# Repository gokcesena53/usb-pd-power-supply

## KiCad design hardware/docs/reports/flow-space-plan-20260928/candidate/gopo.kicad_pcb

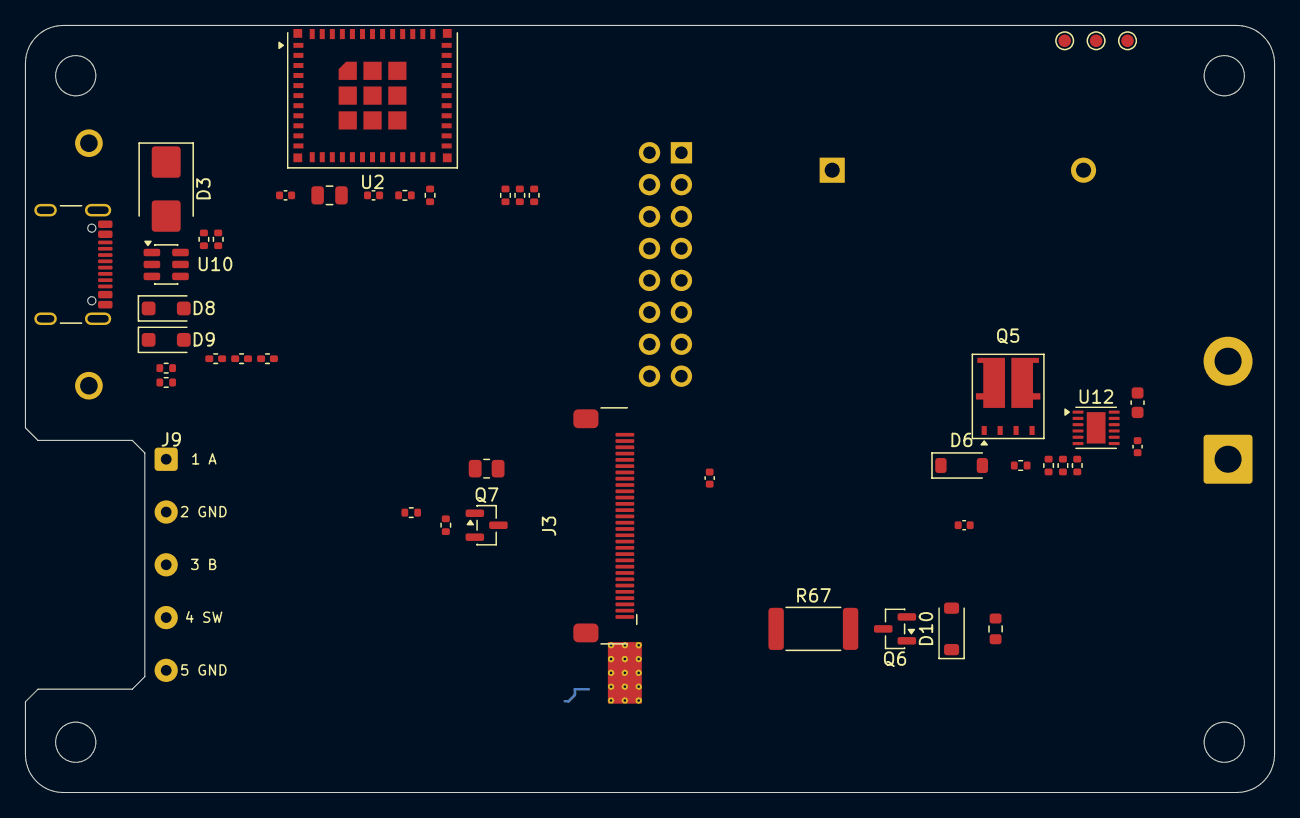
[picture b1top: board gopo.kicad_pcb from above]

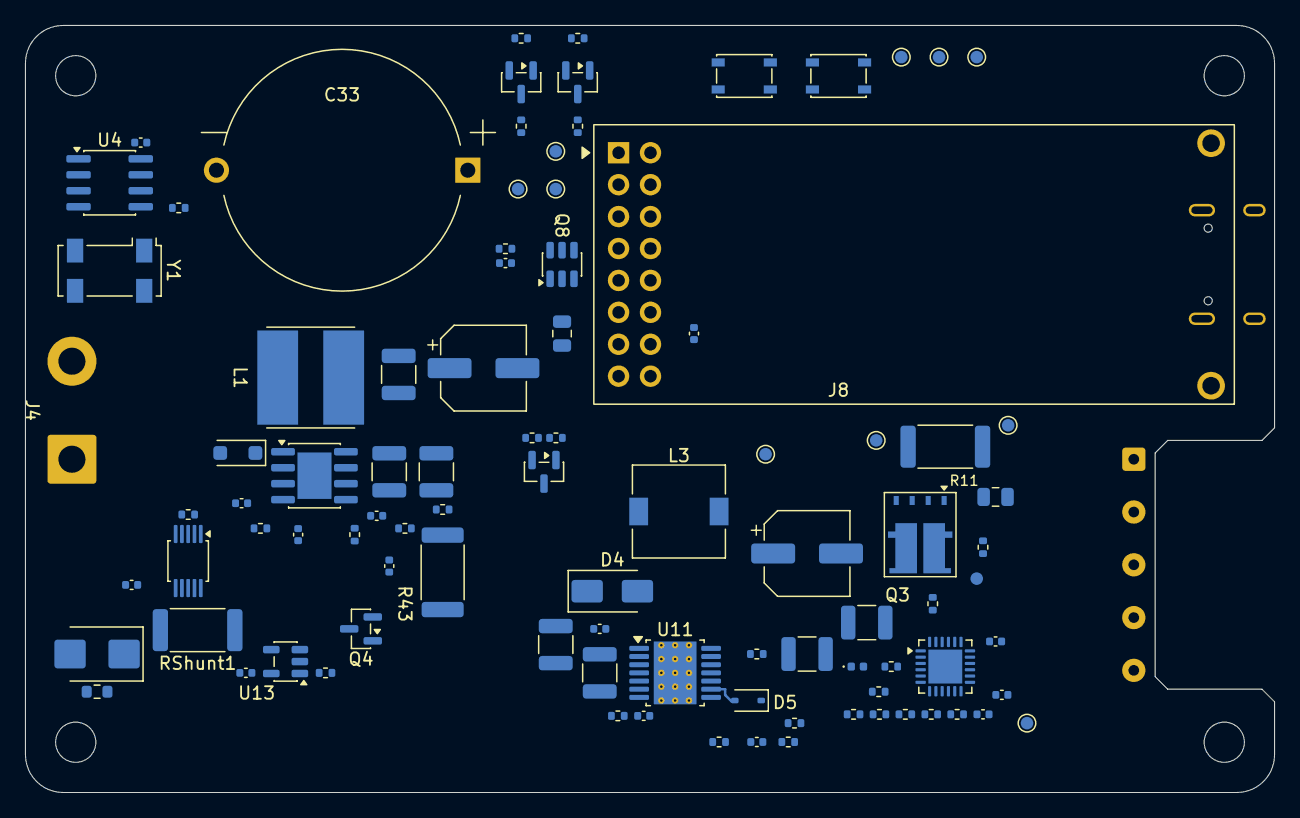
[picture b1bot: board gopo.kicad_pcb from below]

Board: 4 copper layers, 99.4 x 61.0 mm, 144 parts (94 on the bottom side), 86 nets.

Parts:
C1, C2, C6, C11, C14, C17, C20, C21, C24, C26, C32, C35: 100n; C_0402_1005Metric
C3: 2u2; C_0805_2012Metric
C4, C7, C9, C34: 1u0; C_0402_1005Metric
C5, C10: 22u; C_0805_2012Metric
C8, C12, C13, C25, C27, C28: 4u7; C_1210_3225Metric
C15, C29: 47u; CP_Elec_6.3x5.8
C16: 47u; C_1210_3225Metric
C18: 10n; C_0402_1005Metric
C19: 15n; C_0402_1005Metric
C23: 47n; C_0402_1005Metric
C30: 22n; C_0402_1005Metric
C31: 220n; C_0603_1608Metric
C33: 1F5; Korchip_DCL_H-Type_D19.0mm_P20.00mm_Horizontal
D1: LED; LED_0402_1005Metric
D2: SS2060FL; D_SOD-123F
D3, D7: SMBJ30A; D_SMB
D4: SX36; D_SMA
D5: BAS16H; D_SOD-323
D6, D10: BZT52C12; D_SOD-123
D8, D9: SMF30A; D_SOD-123F
H1, H2, H3, H4: M3; MountingHole_3.2mm_M3
J3: TFT032B018; KLS_L-KLS1-242I-2.0-30_1x30-2MP_P0.50mm_Horizontal
J4: SolderWire-1.5sqmm; SolderWire-1.5sqmm_1x02_P7.8mm_D1.7mm_OD3.9mm
J7: USB_C_Receptacle_USB2.0_16P; USB_C_Receptacle_GCT_USB4105-xx-A_16P_TopMnt_Horizontal
J8: 2-CH UART TO ETH; Waveshare_2-CH_UART_TO_ETH
J9: ENCODER CABLE; SolderWire-0.25sqmm_1x05_P4.2mm_D0.65mm_OD1.7mm
L1: 22u; L_CoreMaster_FPI0705_7.8x7.0mm_H5.0
L3: 6u8; L_7.3x7.3_H4.5
MECH_ENC: PANEL EC1121S; J9 cable
Q1, Q2, Q4, Q6: BSS138P; SOT-23
Q3, Q5: SQJB60EP; Vishay_PowerPAK_SO-8L_Dual
Q7: IRLML6344; SOT-23
Q8: TSM3443CX6; SOT-23-6
R1, R8, R9, R10, R16, R27, R34, R35, R36, R37, R56, R65: 10k; R_0402_1005Metric
R2, R3, R15: 22R; R_0402_1005Metric
R4, R5, R6, R7, R24, R61: 4k7; R_0402_1005Metric
R11: 5m0; R_2512_6332Metric
R12: 6k2; R_0402_1005Metric
R13, R28: 100R; R_0402_1005Metric
R14: 2k2; R_0402_1005Metric
R17, R21, R29, R38, R53, R58: 100k; R_0402_1005Metric
R39: 10k2; R_0402_1005Metric
R40: 3k24; R_0402_1005Metric
R41: 51k; R_0402_1005Metric
R43: 4k7; R_2512_6332Metric
R47: 78k7; R_0402_1005Metric
R48: 30k1; R_0402_1005Metric
R49, R51: 9k76; R_0402_1005Metric
R50: 2k87; R_0402_1005Metric
R52, R64: 2k0; R_0402_1005Metric
R54: 1k0; R_0402_1005Metric
R55: 237k; R_0402_1005Metric
R59, R66: 100k; R_0603_1608Metric
R60: 5R6; R_0805_2012Metric
R62, R63: 5k1; R_0402_1005Metric
R67: 1k; R_2512_6332Metric
RShunt1: 5m0; R_2512_6332Metric
SW1: BOOT / PTS810; SW_SPST_PTS810
SW2: RESET / PTS810; SW_SPST_PTS810
TH1: 10k NTC; R_0402_1005Metric
TP1, TP2, TP3, TP4, TP5, TP6, TP7, TP8, TP9, TP10, TP11, TP12, TP13, TP14: TestPoint; TestPoint_Pad_D1.0mm
U1: AP33772SDKZ-13-FA02; Texas_RTW_WQFN-24-1EP_4x4mm_P0.5mm_EP2.7x2.7mm
U2: ESP32-C6-MINI-1-H4; ESP32-C6-MINI-1
U3: INA226; TSSOP-10_3x3mm_P0.5mm
U4: BQ32000; SOIC-8_3.9x4.9mm_P1.27mm
U5: AOZ1284PI; SOIC-8-1EP_3.9x4.9mm_P1.27mm_EP2.71x3.7mm
U6: TLV431BQDBZT; SOT-23
U10: USBLC6-2SC6; SOT-23-6
U11: TPS55340PWPR; Texas_HTSSOP-14-1EP_4.4x5mm_P0.65mm_EP3.4x5mm_Mask3.155x3.2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
U12: LM74801-Q1; WSON-12-1EP_3x3mm_P0.5mm_EP1.5x2.5mm
U13: 74LVC1G08; SOT-23-5
Y1: 32.768kHz; Crystal_SMD_Abracon_ABS25-4Pin_8.0x3.8mm

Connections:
+3.3V: C5.1, C6.1, C9.1, C11.1, C15.1, C16.1, C21.1, C34.1, C35.1, J3.21, J3.22, J3.23, L1.2, Q1.1 (G), Q2.1 (G), Q8.4, R1.1, R4.2, R7.1, R10.2, R17.1, R24.1, R27.1, R34.1, R35.1, R36.1, R37.2, R39.1, R60.1, U2.3, U3.6 (VS), U4.8, U10.5, U13.5
/MCU/ETH_3V3: C10.1, C20.1, J8.13, J8.14, Q8.1, Q8.2, Q8.5, Q8.6
/MCU/ETH_CFG0: J8.3, R15.2, TP9.1 (1_1)
/MCU/ETH_PWR_EN: C21.2, Q8.3, R16.1, R17.2, TP10.1 (1_1)
/MCU/ETH_RUN: J8.4, TP14.1
/MCU/RTC_INT: R24.2, U2.5, U4.7
/MCU/UART_RX: J8.7, TP12.1, U2.30
/MCU/UART_TX: J8.5, TP11.1, U2.31
/USB_PD_CONTROLLER/BOOST_FB: D5.2, R48.2, R49.1, U11.9
/USB_PD_CONTROLLER/BOOST_SW: D4.2, L3.1, U11.1, U11.2
/USB_PD_CONTROLLER/COMP_NODE: R41.1, U5.5 (COMP)
/USB_PD_CONTROLLER/DGATE: Q5.4, U12.1
/USB_PD_CONTROLLER/DISCH_G: D10.1, Q4.3, Q6.1, R66.2
/USB_PD_CONTROLLER/EN_CTRL: D5.1, R43.2, R50.1, U5.8 (EN), U6.2 (REF)
/USB_PD_CONTROLLER/FB_3V3: R39.2, R40.1, U5.6 (FB)
/USB_PD_CONTROLLER/FSW_SET: R38.1, U5.4 (FSW)
/USB_PD_CONTROLLER/GATE_DRV: D6.1, Q5.2, R54.1, U12.8
/USB_PD_CONTROLLER/LX_SW: C17.2, D2.1 (K), L1.1, U5.1 (LX)
/USB_PD_CONTROLLER/OV_SENSE: R55.2, R56.1, U12.5
/USB_PD_CONTROLLER/PD_GATE: Q3.2, Q3.4, R12.2, TP5.1 (1_1)
/USB_PD_CONTROLLER/PD_VBUS_SENSED: C3.1, Q3.7, Q3.8, Q5.7, Q5.8, R11.2, R55.1, TP2.1 (1_1), U1.24 (VCC)
/USB_PD_CONTROLLER/SRC_COMMON: D6.2, Q5.1, Q5.3, U12.2, U12.9
/USB_PD_CONTROLLER/SS_RAMP: C18.1, U5.7 (SS)
/USB_PD_CONTROLLER/SW_EN: Q4.1, R58.1, U12.6, U13.4
/USB_PD_CONTROLLER/SW_OUT: Q5.5, Q5.6, R66.1, RShunt1.1, U3.10 (Vin+), U12.12
/USER INTERFACE/BL_A: J3.2, R60.2
/USER INTERFACE/BL_K: J3.4, Q7.3
ENCODER_A: J9.1, R34.2, U2.28
ENCODER_B: J9.3, R35.2, U2.29
ENCODER_SW: J9.4, R36.2, U2.27
GND: C1.2, C2.2, C3.2, C4.2, C5.2, C6.2, C7.1, C8.2, C9.2, C10.2, C11.2, C12.2, C13.2, C14.2, C15.2, C16.2, C18.2, C19.2, C20.2, C23.2, C24.2, C25.2, C26.2, C27.2, C28.2, C29.2, C30.2, C32.2, C33.2, C34.2, C35.2, D1.1 (K), D2.2 (A), D3.2, D7.2, D8.2, D9.2, D10.2, J3.5, J3.7, J3.8, J3.9, J3.10, J3.11, J3.12, J3.13, J3.14, J3.15, J3.25, J3.30, J4.2, J7.A1 (GND), J7.A12 (GND), J7.B1 (GND), J7.B12 (GND), J7.SH (SHIELD), J8.11, J8.12, J9.2, J9.5, Q4.2, Q6.2, Q7.2, R21.1, R29.2, R38.2, R40.2, R47.2, R49.2, R51.2, R56.2, R58.2, R59.2, R61.2, R62.2, R63.2, R65.2, SW1.1, SW2.1, TH1.1, TP13.1, U1.3 (GND), U1.25 (GND), U2.1, U2.2, U2.11, U2.14, U2.36, U2.37, U2.38, U2.39, U2.40, U2.41, U2.42, U2.43, U2.44, U2.45, U2.46, U2.47, U2.48, U2.49, U2.50, U2.51, U2.52, U2.53, U3.1 (A1), U3.2 (A0), U3.7 (GND), U4.4, U5.3 (GND), U6.3 (A), U10.2, U11.6, U11.7, U11.11, U11.12, U11.13, U11.14, U11.15, U12.7, U13.3, Y1.2, Y1.3
INA_ALERT: R27.2, U2.6, U3.3 (~Alert), U13.2
unnamed: C19.1, R41.2
unnamed: C24.1, R52.2
unnamed: C30.1, R54.2
unnamed: D1.2 (A), R14.2
unnamed: Q3.1, Q3.3
unnamed: Q6.3, R67.2
unnamed: Q7.1, R28.2, R29.1
unnamed: R8.2, R64.1
unnamed: R9.2, R65.1
unnamed: C2.1, U1.15 (IFB)
unnamed: R14.1, U1.8 (LED)
unnamed: TH1.2, U1.13 (OTP)
unnamed: R12.1, U1.23 (PWR_EN)
unnamed: C1.1, U1.12 (V18)
unnamed: R13.1, U1.22 (VOUT)
unnamed: R21.2, U1.11 (VSEL)
unnamed: C7.2, R1.2, SW2.2, U2.8
unnamed: R16.2, U2.12
unnamed: R15.1, R37.1, U2.22
unnamed: R10.1, SW1.2, U2.23
unnamed: R2.1, U2.17
unnamed: R3.1, U2.18
unnamed: U4.1, Y1.1
unnamed: U4.2, Y1.4
unnamed: C33.1, U4.3
unnamed: C17.1, U5.2 (BST)
unnamed: R50.2, R51.1, U6.1 (K)
unnamed: R52.1, U11.8
unnamed: R53.2, U11.4
unnamed: R47.1, U11.10
unnamed: C23.1, U11.5
unnamed: C31.2, U12.11
OUT_EN: R61.1, U2.15, U13.1
OUT_POS: D7.1, J4.1, R59.1, R67.1, RShunt1.2, U3.8 (Vbus), U3.9 (Vin-)
PD_5V: C4.1, R5.1, R6.1, TP4.1 (1_1), U1.20 (V5V)
PD_I2C_SCL_3V3: Q1.2 (S), R4.1, TP6.1 (1_1), U2.24, U3.5 (SCL), U4.6
PD_I2C_SCL_5V: Q1.3 (D), R5.2, U1.5 (SCL)
PD_I2C_SDA_3V3: Q2.2 (S), R7.2, TP7.1 (1_1), U2.25, U3.4 (SDA), U4.5
PD_I2C_SDA_5V: Q2.3 (D), R6.2, U1.4 (SDA)
PD_INT_3V3: R9.1, R64.2, TP8.1 (1_1), U2.26
PD_INT_5V: R8.1, U1.9 (INT)
PD_VOUT: C8.1, C25.1, C26.1, C29.1, L3.2, Q3.5, Q3.6, R13.2, R53.1, TP3.1 (1_1), U11.3
TFT_BL_PWM: R28.1, U2.13
TFT_CS: J3.18, U2.19
TFT_DC: J3.16, U2.16
TFT_MOSI: J3.19, U2.10
TFT_RST: J3.20, U2.20
TFT_SCLK: J3.17, U2.9
USB_CC1: D8.1, J7.A5 (CC1), R62.1, U1.17 (CC1)
USB_CC2: D9.1, J7.B5 (CC2), R63.1, U1.16 (CC2)
USB_DM: J7.A7 (D-), J7.B7 (D-), R2.2, U10.1, U10.6
USB_DP: J7.A6 (D+), J7.B6 (D+), R3.2, U10.3, U10.4
USB_VBUS: D3.1, J7.A4 (VBUS), J7.A9 (VBUS), J7.B4 (VBUS), J7.B9 (VBUS), R11.1, TP1.1 (1_1), U1.1 (ISENP)
V_PRE: C12.1, C13.1, C14.1, C27.1, C28.1, C31.1, C32.1, D4.1, R43.1, R48.1, U5.9 (VIN), U12.3, U12.4, U12.10

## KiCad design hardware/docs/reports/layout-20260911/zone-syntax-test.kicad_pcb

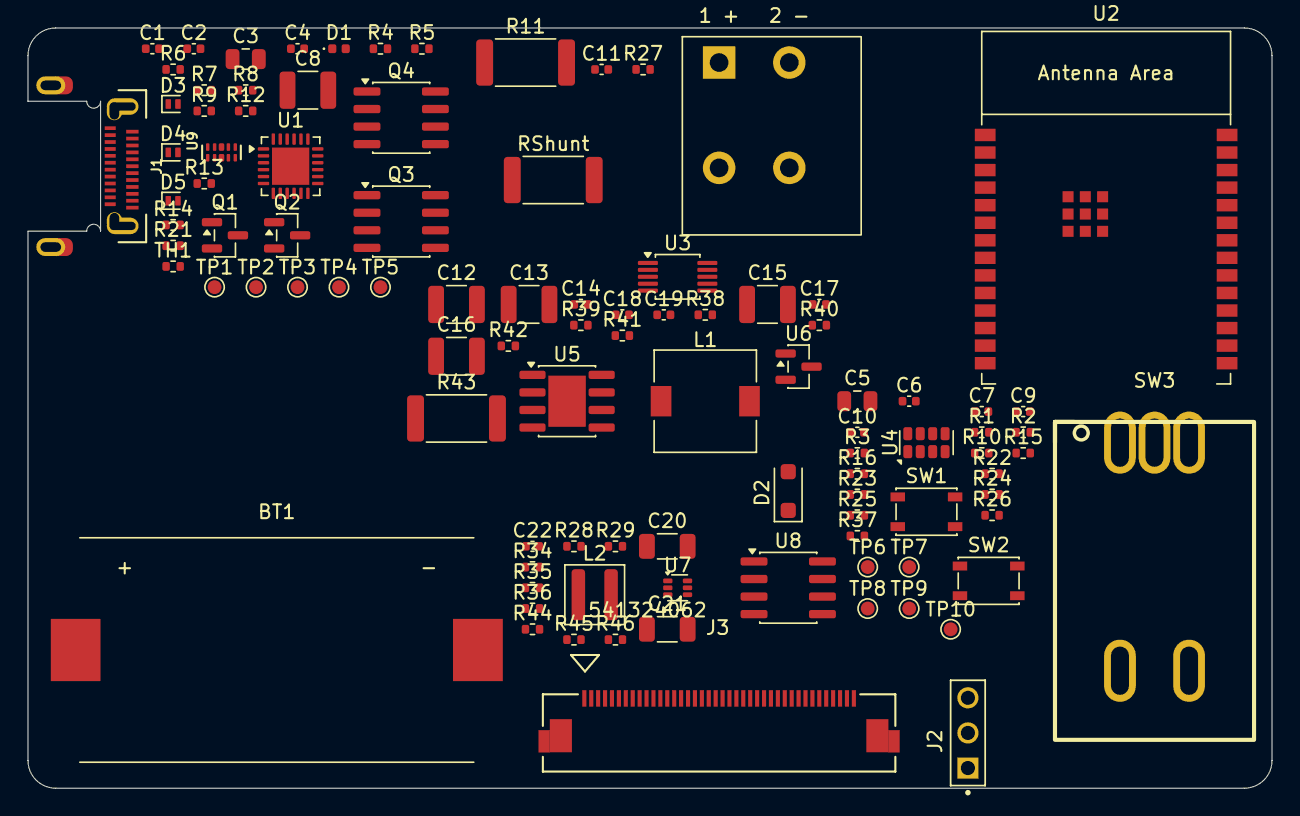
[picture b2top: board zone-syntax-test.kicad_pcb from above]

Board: 4 copper layers, 90.0 x 55.0 mm, 100 parts (0 on the bottom side), 70 nets, no tracks yet.

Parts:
BT1: CR2032 holder; KLS_CR2032_05
C1, C2: 100 nF; C_0402_1005Metric
C3: 1uF / 50V; C_0805_2012Metric
C4: 1uF / 10V; C_0402_1005Metric
C5: 22uF; C_0805_2012Metric
C6, C9, C10, C11, C14: 100nF; C_0402_1005Metric
C7: 1uF; C_0402_1005Metric
C8: 10uF / 50V; C_1210_3225Metric
C12, C13: 10uF; C_1210_3225Metric
C15, C16: 47uF; C_1210_3225Metric
C17, C22: 100nF / 16V; C_0402_1005Metric
C18: 10nF; C_0402_1005Metric
C19: 18nF / 16V; C_0402_1005Metric
C20, C21: 22uF; C_1206_3216Metric
D1: LED; LED_0402_1005Metric
D2: SS2060FL_R1_00001; D_SOD-123F
D3, D4, D5: AQ3130E-01ETG (bidirectional); D_SOD-882
J1: DX07B024JJ1R1500; JAE_DX07B024JJ1R1500
J2: DS1021-1X3SF11-B; CONNFLY_DS1021-1X3SF11-B
J3: NHD-2.4-240320AF-CSXP; CON_541324062_MOL
J4: DG142R-5.08-02P-14-00AH
L1: SRI0704-220M; L_7.3x7.3_H4.5
L2: 2.2uH; L_Wuerth_MAPI-4030
Q1, Q2: BSS138; SOT-23
Q3, Q4: IRF7855TRPBF; SOIC-8_3.9x4.9mm_P1.27mm
R1: 10 kΩ; R_0402_1005Metric
R2, R3: 22Ω; R_0402_1005Metric
R4: 4.7 kΩ; R_0402_1005Metric
R5: 4.7kΩ; R_0402_1005Metric
R6: 4.7 k; R_0402_1005Metric
R7, R25: 4.7k; R_0402_1005Metric
R8: 12k; R_0402_1005Metric
R9: 20k; R_0402_1005Metric
R10, R23, R34, R35, R36: 10k; R_0402_1005Metric
R11: 5mR / 1W; R_2512_6332Metric
R12: 6.2k; R_0402_1005Metric
R13, R28: 100R; R_0402_1005Metric
R14: 2.2k; R_0402_1005Metric
R15: 22 R; R_0402_1005Metric
R16: 22R; R_0402_1005Metric
R21: 100K; R_0402_1005Metric
R22: 1K; R_0402_1005Metric
R24: 4,7k; R_0402_1005Metric
R26: 4.7K; R_0402_1005Metric
R27: 10K; R_0402_1005Metric
R29, R42: 100kR; R_0402_1005Metric
R37: 10kR; R_0402_1005Metric
R38: 100kR 1%; R_0402_1005Metric
R39: 10kR 0.1%; R_0402_1005Metric
R40: 3.20kR 0.1%; R_0402_1005Metric
R41: 12.7kR 1%; R_0402_1005Metric
R43: 1kR / 2W; R_2512_6332Metric
R44: 604kR 0.1%; R_0402_1005Metric
R45: 100kR 0.1%; R_0402_1005Metric
R46: 3.24kR 0.1%; R_0402_1005Metric
RShunt: 5mR / 1W; R_2512_6332Metric
SW1: BOOT / PTS810; SW_SPST_PTS810
SW2: RESET / PTS810; SW_SPST_PTS810
SW3: L-KLS4-EC12-012424-W
TH1: TSM0B103F3381RZ / 10k NTC; R_0402_1005Metric
TP1, TP2, TP3, TP4, TP5, TP6, TP7, TP8, TP9, TP10: TestPoint; TestPoint_Pad_D1.0mm
U1: AP33772SDKZ-13-FA02; Texas_RTW_WQFN-24-1EP_4x4mm_P0.5mm_EP2.7x2.7mm
U2: ESP32-C6-WROOM-1
U3: INA228; TSSOP-10_3x3mm_P0.5mm
U4: RV-3028-C7; MicroCrystal_C7_SON-8_1.5x3.2mm_P0.9mm
U5: AOZ1284PI; SOIC-8-1EP_3.9x4.9mm_P1.27mm_EP2.71x3.7mm
U6: TL431BIDBZR; SOT-23
U7: TPS61023DRLR; SOT-563
U8: CAT4104V-GT3; SOIC-8_3.9x4.9mm_P1.27mm
U9: TPD4E05U06QDQARQ1; antmicro_tpd4e05u06qdqarq1

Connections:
+3.3V: C5.1, C6.1, C9.1, C11.1, C15.1, C16.1, C20.1, J3.7, J3.8, J3.32, J3.33, L1.2, L2.1, Q1.1, Q2.1, R1.1, R4.2, R7.1, R10.2, R24.1, R25.1, R26.2, R27.1, R34.1, R35.1, R36.1, R37.1, R39.1, U2.2, U3.6, U4.7, U7.2, U7.3
/MCU/RTC_INT: R24.2, U2.27, U4.2
/MCU/RTC_SCL: R25.2, U2.7, U4.3
/MCU/RTC_SDA: R26.1, U2.6, U4.4
/MCU/UART_RX: J2.2, U2.24
/MCU/UART_TX: J2.1, U2.25
/POWER GENERATION/COMP_NODE: R41.1, U5.5
/POWER GENERATION/EN_CTRL: R42.1, R43.2, U5.8, U6.1, U6.2
/POWER GENERATION/FB_3V3: R39.2, R40.1, U5.6
/POWER GENERATION/FSW_SET: R38.1, U5.4
/POWER GENERATION/LX_SW: C17.2, D2.1, L1.1, U5.1
/POWER GENERATION/SS_RAMP: C18.1, U5.7
/USB_PD_CONTROLLER/PD_GATE: Q3.4, Q4.4, R12.2, TP5.1
/USER INTERFACE/BL_BOOST_FB: R44.2, R45.1, U7.1
/USER INTERFACE/BL_BOOST_SW: L2.2, U7.5
/USER INTERFACE/BL_K1: J3.34, U8.1
/USER INTERFACE/BL_K2: J3.35, U8.2
/USER INTERFACE/BL_K3: J3.36, U8.3
/USER INTERFACE/BL_K4: J3.37, U8.4
BACKLIGHT_4V2: C21.1, C22.1, J3.38, R44.1, U7.6, U8.7
ENCODER_A: R34.2, SW3.1, U2.20
ENCODER_B: R35.2, SW3.3, U2.21
ENCODER_SW: R36.2, SW3.4, U2.19
GND: BT1.2, C1.2, C2.2, C3.2, C4.2, C5.2, C6.2, C7.1, C8.2, C9.2, C10.2, C11.2, C12.2, C13.2, C14.2, C15.2, C16.2, C18.2, C19.2, C20.2, C21.2, C22.2, D1.1, D2.2, D3.1, D4.2, D5.2, J1.A1, J1.A12, J1.B1, J1.B12, J1.SH, J2.3, J3.1, J3.13, J3.14, J3.15, J3.16, J3.17, J3.18, J3.19, J3.20, J3.21, J3.22, J3.23, J3.24, J3.25, J3.26, J3.27, J3.28, J3.29, J3.31, J3.39, J4.2, R9.2, R21.1, R23.2, R29.2, R38.2, R40.2, R42.2, R45.2, R46.2, SW1.1, SW2.1, SW3.2, SW3.5, TH1.1, U1.3, U1.25, U2.1, U2.28, U2.29, U3.1, U3.2, U3.7, U4.5, U5.3, U6.3, U7.4, U8.5, U9.3, U9.8
INA_ALERT: R27.2, U2.26, U3.3
unnamed: BT1.1, R22.2
unnamed: C19.1, R41.2
unnamed: D1.2, R14.2
unnamed: Q3.1, Q3.2, Q3.3, Q4.1, Q4.2, Q4.3
unnamed: R15.2, TP9.1
unnamed: R16.1, TP10.1
unnamed: C2.1, U1.15
unnamed: R14.1, U1.8
unnamed: TH1.2, U1.13
unnamed: R12.1, U1.23
unnamed: C1.1, U1.12
unnamed: R13.1, U1.22
unnamed: R21.2, U1.11
unnamed: C7.2, R1.2, SW2.2, U2.3
unnamed: R16.2, U2.8
unnamed: R15.1, R37.2, U2.10
unnamed: R10.1, SW1.2, U2.15
unnamed: R3.1, U2.13
unnamed: R2.1, U2.14
unnamed: R23.1, U4.8
unnamed: C10.1, R22.1, U4.6
unnamed: C17.1, U5.2
unnamed: R28.2, R29.1, U8.6
unnamed: R46.1, U8.8
OUT_POS: J4.1, RShunt.2, U3.8, U3.9
PD_5V: C4.1, R5.1, R6.1, TP4.1, U1.20
PD_I2C_SCL_3V3: Q1.2, R4.1, TP6.1, U2.16, U3.5
PD_I2C_SCL_5V: Q1.3, R5.2, U1.5
PD_I2C_SDA_3V3: Q2.2, R7.2, TP7.1, U2.17, U3.4
PD_I2C_SDA_5V: Q2.3, R6.2, U1.4
PD_INT_3V3: R8.2, R9.1, TP8.1, U2.18
PD_INT_5V: R8.1, U1.9
PD_VBUS_SENSED: C3.1, Q4.5, Q4.6, Q4.7, Q4.8, R11.2, TP2.1, U1.24
PD_VOUT: C8.1, C12.1, C13.1, C14.1, Q3.5, Q3.6, Q3.7, Q3.8, R13.2, R43.1, RShunt.1, TP3.1, U3.10, U5.9
TFT_BL_PWM: R28.1, U2.9
TFT_CS: J3.10, U2.11
TFT_DC: J3.12, U2.12
TFT_MOSI: J3.9, U2.5
TFT_RST: J3.30, U2.23
TFT_SCLK: J3.11, U2.4
USB_CC1: D4.1, J1.A5, U1.17
USB_CC2: D5.1, J1.B5, U1.16
USB_DM: J1.A7, J1.B7, R3.2, U9.2
USB_DP: J1.A6, J1.B6, R2.2, U9.1
USB_VBUS: D3.2, J1.A4, J1.A9, J1.B4, J1.B9, R11.1, TP1.1, U1.1

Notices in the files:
parts and their libraries:
License: Apache-2.0
